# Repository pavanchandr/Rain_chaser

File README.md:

# Led_chaser
Sequential logic PCB using 555 timer and CD4017

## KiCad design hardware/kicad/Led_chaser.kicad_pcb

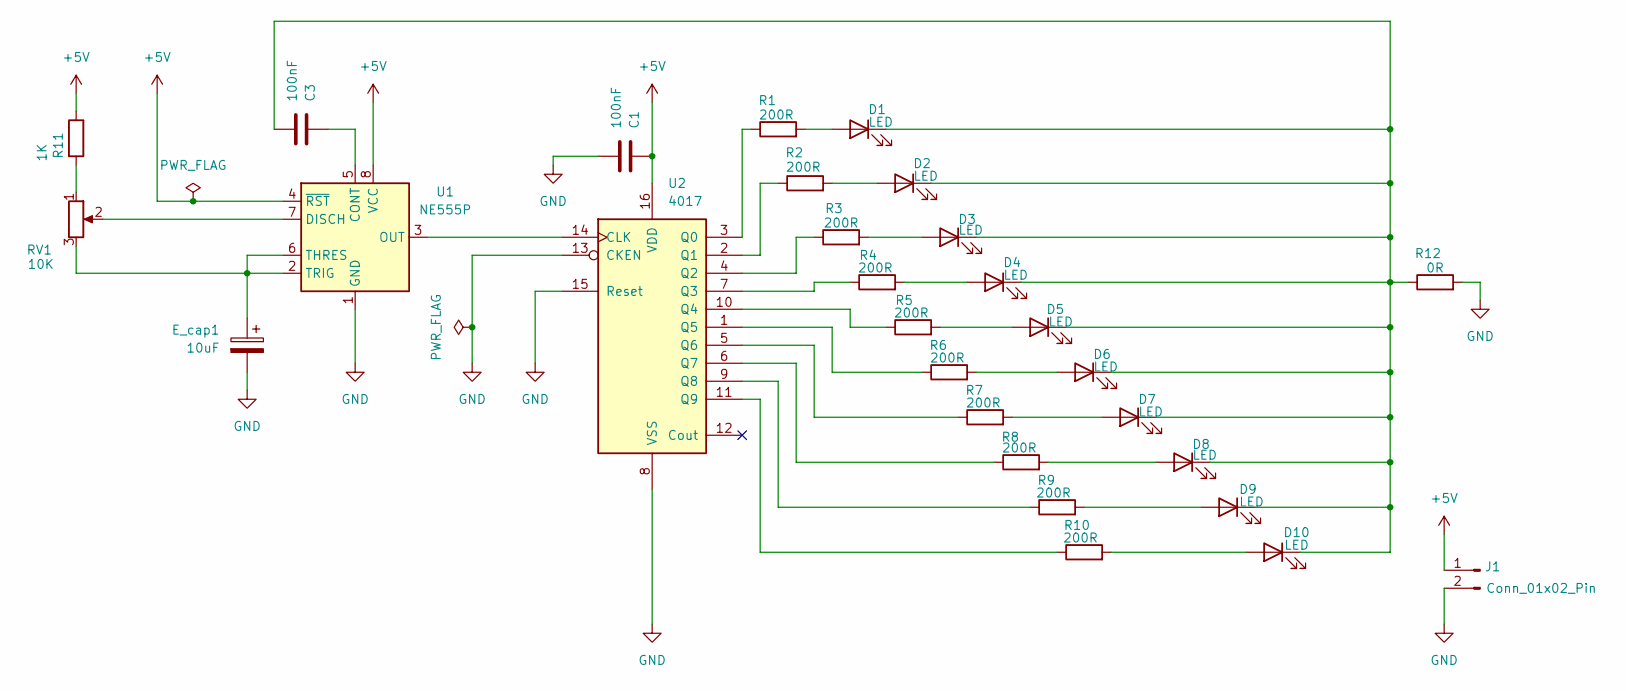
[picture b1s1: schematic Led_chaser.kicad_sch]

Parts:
C1, C3: 100nF; C_Disc_D5.0mm_W2.5mm_P5.00mm
D1, D2, D3, D4, D5, D6, D7, D8, D9, D10: LED; LED_D5.0mm
E_cap1: 10uF; CP_Radial_D5.0mm_P2.50mm
J1: Conn_01x02_Pin; AMASS_XT30U-F_1x02_P5.0mm_Vertical
R1, R2, R3, R4, R5, R6, R7, R8, R9, R10: 200R; R_Axial_DIN0207_L6.3mm_D2.5mm_P7.62mm_Horizontal
R11: 1K; R_Axial_DIN0207_L6.3mm_D2.5mm_P7.62mm_Horizontal
R12: 0R; R_Axial_DIN0207_L6.3mm_D2.5mm_P7.62mm_Horizontal
RV1: 10K; Potentiometer_Alps_RK09K_Single_Vertical
U1: NE555P; DIP-8_W7.62mm
U2: 4017; CERDIP-16_W7.62mm_SideBrazed

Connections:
+5V: C1.1, J1.1, R11.1, U1.4 (~RST), U1.8 (VCC), U2.16 (VDD)
GND: C1.2, E_cap1.2, J1.2, R12.2, U1.1 (GND), U2.8 (VSS), U2.13 (CKEN), U2.15 (Reset)
unnamed: D1.2 (A), R1.2
unnamed: C3.2, D1.1 (K), D2.1 (K), D3.1 (K), D4.1 (K), D5.1 (K), D6.1 (K), D7.1 (K), D8.1 (K), D9.1 (K), D10.1 (K), R12.1
unnamed: D2.2 (A), R2.2
unnamed: D3.2 (A), R3.2
unnamed: D4.2 (A), R4.2
unnamed: D5.2 (A), R5.2
unnamed: D6.2 (A), R6.2
unnamed: D7.2 (A), R7.2
unnamed: D8.2 (A), R8.2
unnamed: D9.2 (A), R9.2
unnamed: D10.2 (A), R10.2
unnamed: R11.2, RV1.1
unnamed: C3.1, U1.5 (CONT)
unnamed: RV1.2, U1.7 (DISCH)
unnamed: U1.3 (OUT), U2.14 (CLK)
unnamed: E_cap1.1, RV1.3, U1.2 (TRIG), U1.6 (THRES)
unnamed: R1.1, U2.3 (Q0)
unnamed: R2.1, U2.2 (Q1)
unnamed: R3.1, U2.4 (Q2)
unnamed: R4.1, U2.7 (Q3)
unnamed: R5.1, U2.10 (Q4)
unnamed: R6.1, U2.1 (Q5)
unnamed: R7.1, U2.5 (Q6)
unnamed: R8.1, U2.6 (Q7)
unnamed: R9.1, U2.9 (Q8)
unnamed: R10.1, U2.11 (Q9)

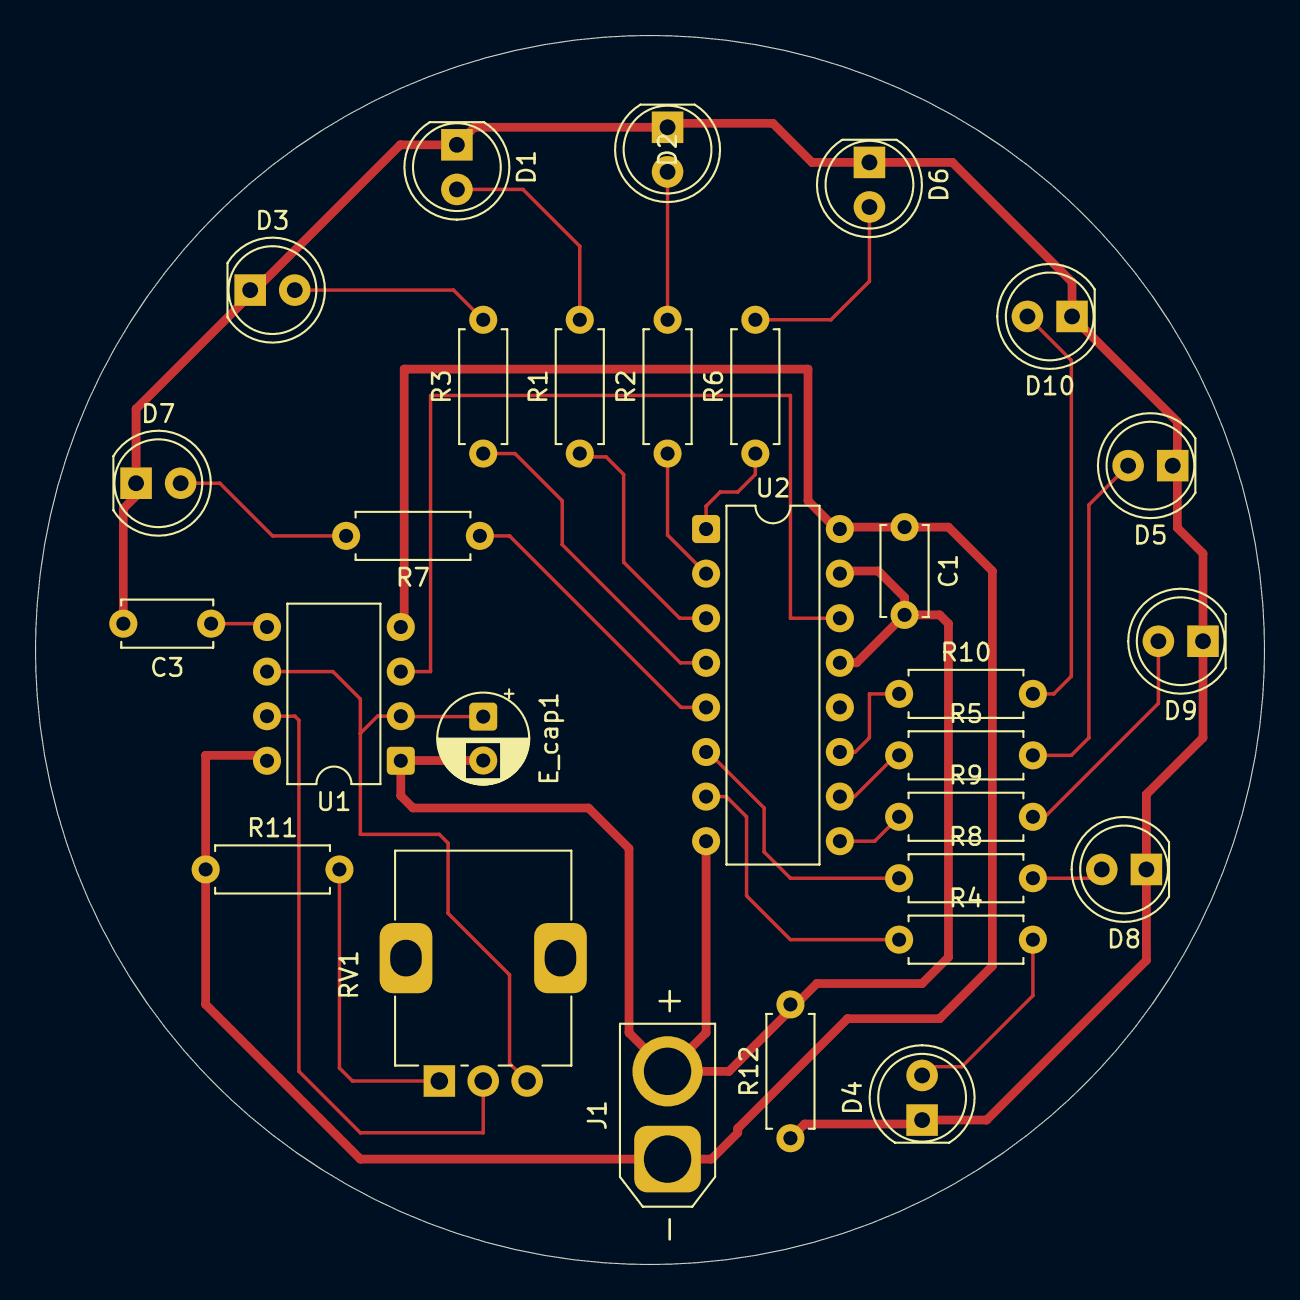
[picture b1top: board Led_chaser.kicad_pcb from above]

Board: 2 copper layers, 70.0 x 70.0 mm, 29 parts (0 on the bottom side), 28 nets.

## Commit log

2026-03-31 Rename project from Rain_chaser to Led_chaser
2026-04-07 Create kicad
2026-04-07 Create gerber
2026-04-07 Create images
2026-04-07 Rename Led_chaser.kicad_pcb to hardware/kicad/Led_chaser.kicad_pcb
2026-04-07 Rename Led_chaser.kicad_pro to hardware/kicad/Led_chaser.kicad_pro
2026-04-07 Rename Led_chaser.kicad_sch to hardware/kicad/Led_chaser.kicad_sch
2026-04-07 Rename Led_chaser_Gerber_Drill.zip to hardware/gerber/Led_chaser_Gerber_Drill.zip
2026-04-07 Rename Led_chaser_pcb.png to images/Led_chaser_pcb.png
2026-04-07 Rename Ledchaser_pcb_2D.png to images/Ledchaser_pcb_2D.png
2026-04-07 Rename Ledchaser_schm.png to images/Ledchaser_schm.png
